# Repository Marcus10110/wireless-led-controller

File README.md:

# wireless-led-pcb

Dirt Simple LED Controller.

ESP32 based.

Supports running from a single 18650 battery, or a barrel jack.

For 18650 operation, only 5V strips are supported.

For barrel jack operation, 5V, 12V, and 24V strips are supported.

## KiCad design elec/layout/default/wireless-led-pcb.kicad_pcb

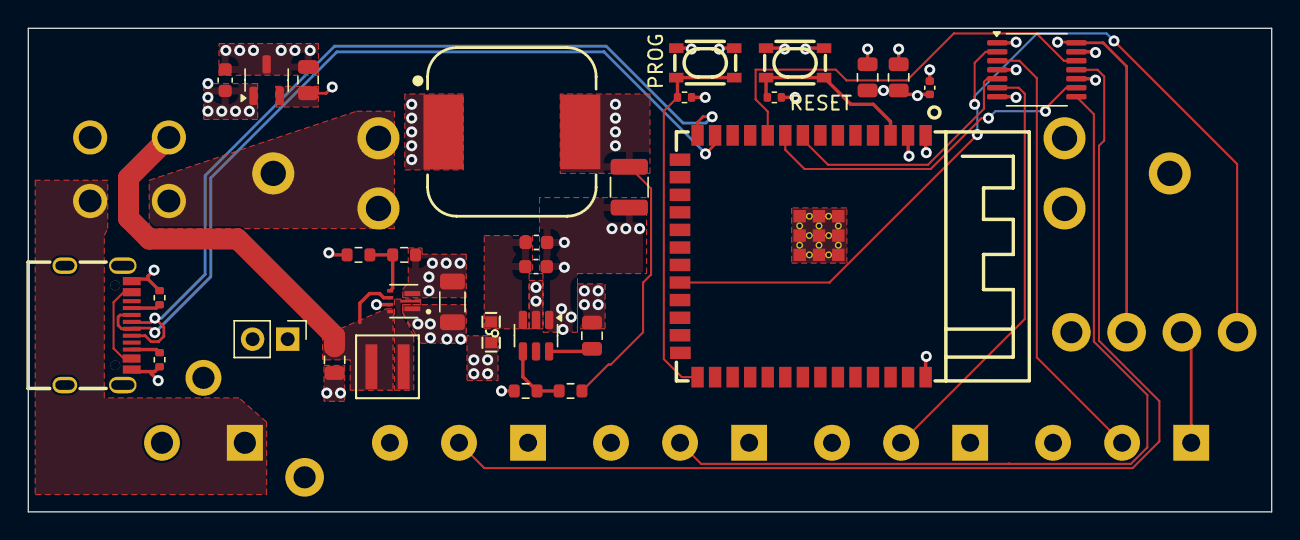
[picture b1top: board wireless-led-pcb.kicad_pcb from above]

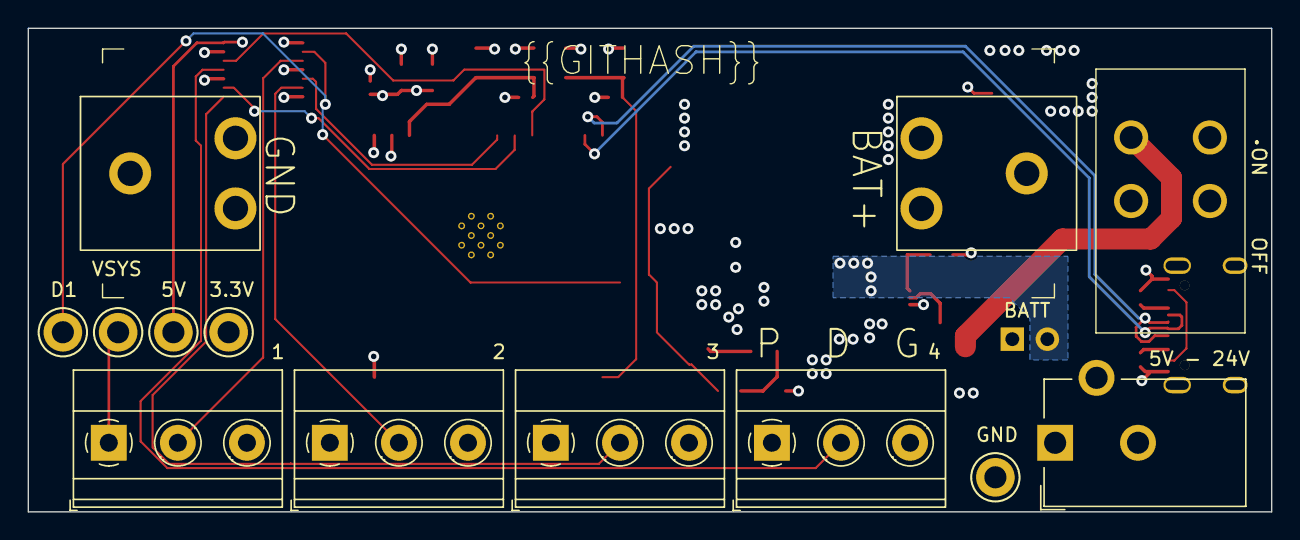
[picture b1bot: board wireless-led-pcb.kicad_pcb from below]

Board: 4 copper layers, 90.0 x 35.0 mm, 43 parts (12 on the bottom side), 29 nets.

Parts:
C1: 16V 100nF X7R ±10% 0402 Multilayer Ceramic Capaci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; C0402
C2, C3, C4, C11: 25V 10uF X5R ±10% 0805 Multilayer Ceramic Capacit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; C0805
C5: 10V 47uF X5R ±20% 1206 Multilayer Ceramic Capacit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; C1206
C6: 25V 3.3uF X5R ±10% 0603 Multilayer Ceramic Capaci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; C0603
C7: 50V 100nF X7R ±10% 0603 Multilayer Ceramic Capaci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; C0603
C8: 16V 47uF X7R ±10% 1210 Multilayer Ceramic Capacit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; C1210
C9: 50V 100nF X7R ±10% 0805 Multilayer Ceramic Capaci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; C0805
C10: 50V 1uF X5R ±10% 0603 Multilayer Ceramic Capacito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; C0603
J1, J2, J3, J4, J5: TestPoint_Keystone_5005-5009_Compact
L1: 1uH +/- 20%; IND_XAL4020_COC
L2: 10uH +/- 20%; WE-PD_1260
R1, R2: 62.5mW Thick Film Resistors 50V ±100ppm/℃ ±1% 4.7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; R0402
R3, R8: 62.5mW Thick Film Resistors 50V ±100ppm/℃ ±1% 10k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; R0402
R4: 100mW Thick Film Resistors 75V ±100ppm/℃ ±1% 732k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; R0603
R5, R7: 100mW Thick Film Resistors 75V ±100ppm/℃ ±1% 100k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; R0603
R6: 100mW Thick Film Resistors 75V ±100ppm/℃ ±1% 22kΩ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; R0603
U1: USB-C-SMD_KH-TYPE-C-16P
U2: WIRELM-SMD_ESP32-S3-WROOM-1
U3, U17: KEY-SMD_4P-L4.2-W3.2-P2.20-LS4.6
U4: TSSOP-14_4.4x5mm_P0.65mm
U5: Battery-54
U6: BarrelJack_CUI_PJ-102AH_Horizontal
U7, U8, U9, U10: TerminalBlock_Phoenix_MKDS-1,5-3_1x03_P5.00mm_Horizontal
U11: L201011MS02Q
U12: CONV_TPS61022RWUR
U13: SOT-23-6
U14: F0603
U15: PinHeader_1x02_P2.54mm_Vertical
U16: SOT-23-3

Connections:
3V3: C1.1, C2.1, C3.1, C8.1, J2.1, L2.2, R3.1, R7.1, R8.1, U2.2
5V: C5.1, R4.1, U12.3, U15.2
BOOT: R8.2, U2.27, U17.1, U17.2
D_N: U1.A7, U1.B7, U2.13
D_P: U1.A6, U1.B6, U2.14
FB_BOOST: R4.2, R5.1, U12.4
FB_BUCK: R6.1, R7.2, U13.4
GND: C1.2, C2.2, C3.2, C4.2, C5.2, C6.2, C7.2, C8.2, C10.2, C11.2, J1.1, R1.2, R2.2, R5.2, R6.2, U1.1, U1.2, U1.3, U1.4, U1.A1, U1.A12, U1.B1, U1.B12, U2.1, U2.40, U2.41, U3.3, U3.4, U4.1, U4.4, U4.7, U4.10, U4.13, U5.2, U6.2, U7.3, U8.3, U9.3, U10.3, U12.1, U12.6, U13.1, U16.3, U17.3, U17.4
LED1: U4.3, U7.2
LED1_LV: J4.1, U2.22, U4.2
LED2: U4.6, U8.2
LED2_LV: U2.8, U4.5
LED3: U4.8, U9.2
LED3_LV: U2.9, U4.9
LED4: U4.11, U10.2
LED4_LV: U2.10, U4.12
SW_BOOST: L1.2, U12.2
SW_BUCK: C9.2, L2.1, U13.2
V5_LDO: C11.1, J3.1, U4.14, U16.2
VBAT: U5.1, U11.5
VBAT_SW: C4.1, L1.1, U11.4, U12.5, U12.7
VIN_BUCK: C6.1, C7.1, U13.3, U14.2
VJACK: U6.1, U11.2
VSYS: C10.1, J5.1, U7.1, U8.1, U9.1, U10.1, U11.1, U14.1, U15.1, U16.1
boot: C9.1, U13.6
cc1: R1.1, U1.A5
cc2: R2.1, U1.B5
mcu.ic-en: R3.2, U2.3, U3.1, U3.2
vcc: U1.A4, U1.A9, U1.B4, U1.B9

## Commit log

2024-07-03 fixed build errors
2024-07-04 moving stuff around in circles...
2024-07-04 adding footprints (unverified)
2024-07-04 added both switching power supplies, implemented most of the hookup.
2024-07-04 added LDO
2024-07-05 fixed up kicad footprints, added manual footprints for inductors.
2024-07-05 Just started basic component organization in the layout. 1% done.
2024-07-06 lots of little schematic fixes.
2024-07-06 Layout "done" but tbh it's super unverified.
2024-07-06 messing around with ato view.
2024-07-06 more messing around with ato view..
2024-07-07 basic layout complete, smoke tested with jlcpcb.
2024-07-07 added test points
2024-07-07 added missing links
2024-07-07 fixed battery holder footprint to fit longer cell
2024-07-07 removed the high side switch and added a jumper for disconnecting the battery.
2024-07-07 removed extra nest layer.
2024-07-07 added libs as submodules, hopefully this will fix CI errors.
2024-07-07 added submodules to ci script.
2024-07-28 added basic test firmware. It works! (until the buck supply exploded)
2024-07-29 added fuse from JLCPCB and new inductor from digikey.
2024-07-29 added net labels added fuse to buck input removed some testpoints. added extra cap to buck supply changed inductor on buck supply to a MUCH larger one.
2024-07-29 totally new layout, much smaller, tons of pours.
